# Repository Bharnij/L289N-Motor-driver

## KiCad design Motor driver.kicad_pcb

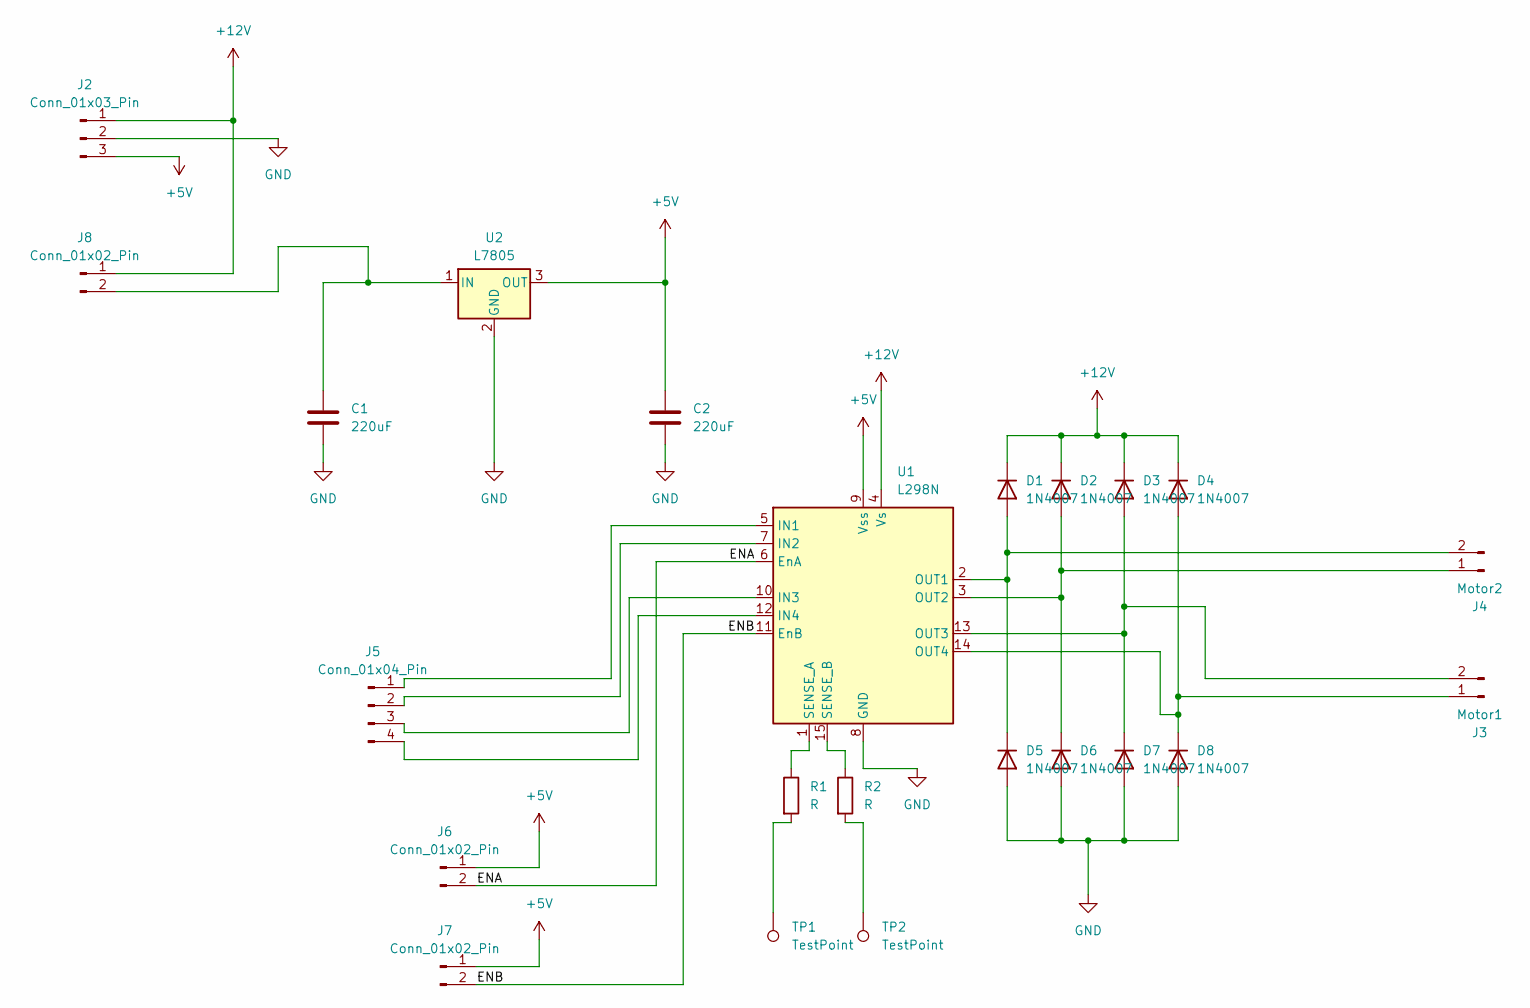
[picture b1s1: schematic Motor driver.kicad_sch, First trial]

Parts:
C1: 220uF; CP_Radial_D5.0mm_P2.50mm
C2: 220uF; CP_Radial_D4.0mm_P1.50mm
D1, D2, D3, D4, D5, D6, D7, D8: 1N4007; D_DO-41_SOD81_P10.16mm_Horizontal
J2: Conn_01x03_Pin; TerminalBlock_Phoenix_MKDS-1-3-3.81_1x03_P3.81mm_Horizontal
J3: Motor1; TerminalBlock_Phoenix_MKDS-1,5-2_1x02_P5.00mm_Horizontal
J4: Motor2; TerminalBlock_Phoenix_MKDS-1,5-2_1x02_P5.00mm_Horizontal
J5: Conn_01x04_Pin; PinSocket_1x04_P2.54mm_Vertical
J6, J7: Conn_01x02_Pin; PinHeader_1x02_P1.27mm_Vertical
J8: Conn_01x02_Pin; PinHeader_1x02_P2.54mm_Vertical
R1, R2: R; R_0603_1608Metric_Pad0.98x0.95mm_HandSolder
TP1, TP2: TestPoint; TestPoint_Keystone_5005-5009_Compact
U1: L298N; TO-220-15_P2.54x5.08mm_StaggerOdd_Lead4.58mm_Vertical
U2: L7805; TO255P1020X450X2000-3

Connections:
+5V: C2.1, J2.3, J6.1, J7.1, U1.9 (Vss), U2.3 (OUT)
+12V: D1.1 (K), D2.1 (K), D3.1 (K), D4.1 (K), J2.1, J8.1, U1.4 (Vs)
/ENA: J6.2, U1.6 (EnA)
/ENB: J7.2, U1.11 (EnB)
GND: C1.2, C2.2, D5.2 (A), D6.2 (A), D7.2 (A), D8.2 (A), J2.2, U1.8 (GND), U2.2 (GND)
unnamed: D1.2 (A), D5.1 (K), J4.2, U1.2 (OUT1)
unnamed: D2.2 (A), D6.1 (K), J4.1, U1.3 (OUT2)
unnamed: D3.2 (A), D7.1 (K), J3.2, U1.13 (OUT3)
unnamed: D4.2 (A), D8.1 (K), J3.1, U1.14 (OUT4)
unnamed: J5.1, U1.5 (IN1)
unnamed: J5.2, U1.7 (IN2)
unnamed: J5.3, U1.10 (IN3)
unnamed: J5.4, U1.12 (IN4)
unnamed: C1.1, J8.2, U2.1 (IN)
unnamed: R1.2, TP1.1 (1_1)
unnamed: R2.2, TP2.1 (1_1)
unnamed: R1.1, U1.1 (SENSE_A)
unnamed: R2.1, U1.15 (SENSE_B)

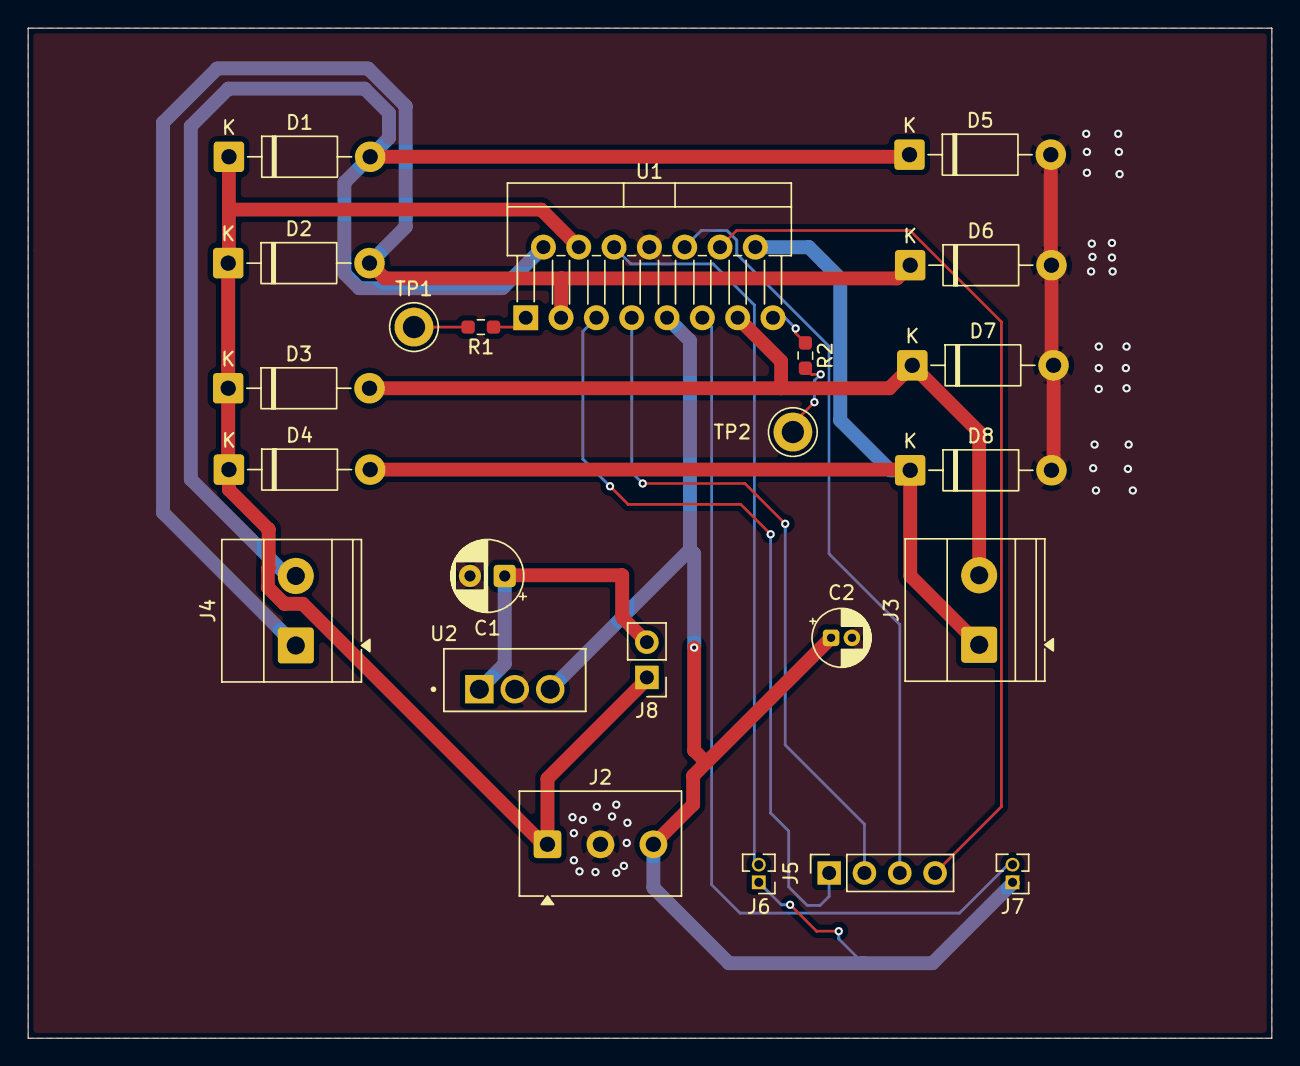
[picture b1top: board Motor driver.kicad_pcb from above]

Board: 2 copper layers, 89.4 x 72.7 mm, 23 parts (0 on the bottom side), 18 nets.
